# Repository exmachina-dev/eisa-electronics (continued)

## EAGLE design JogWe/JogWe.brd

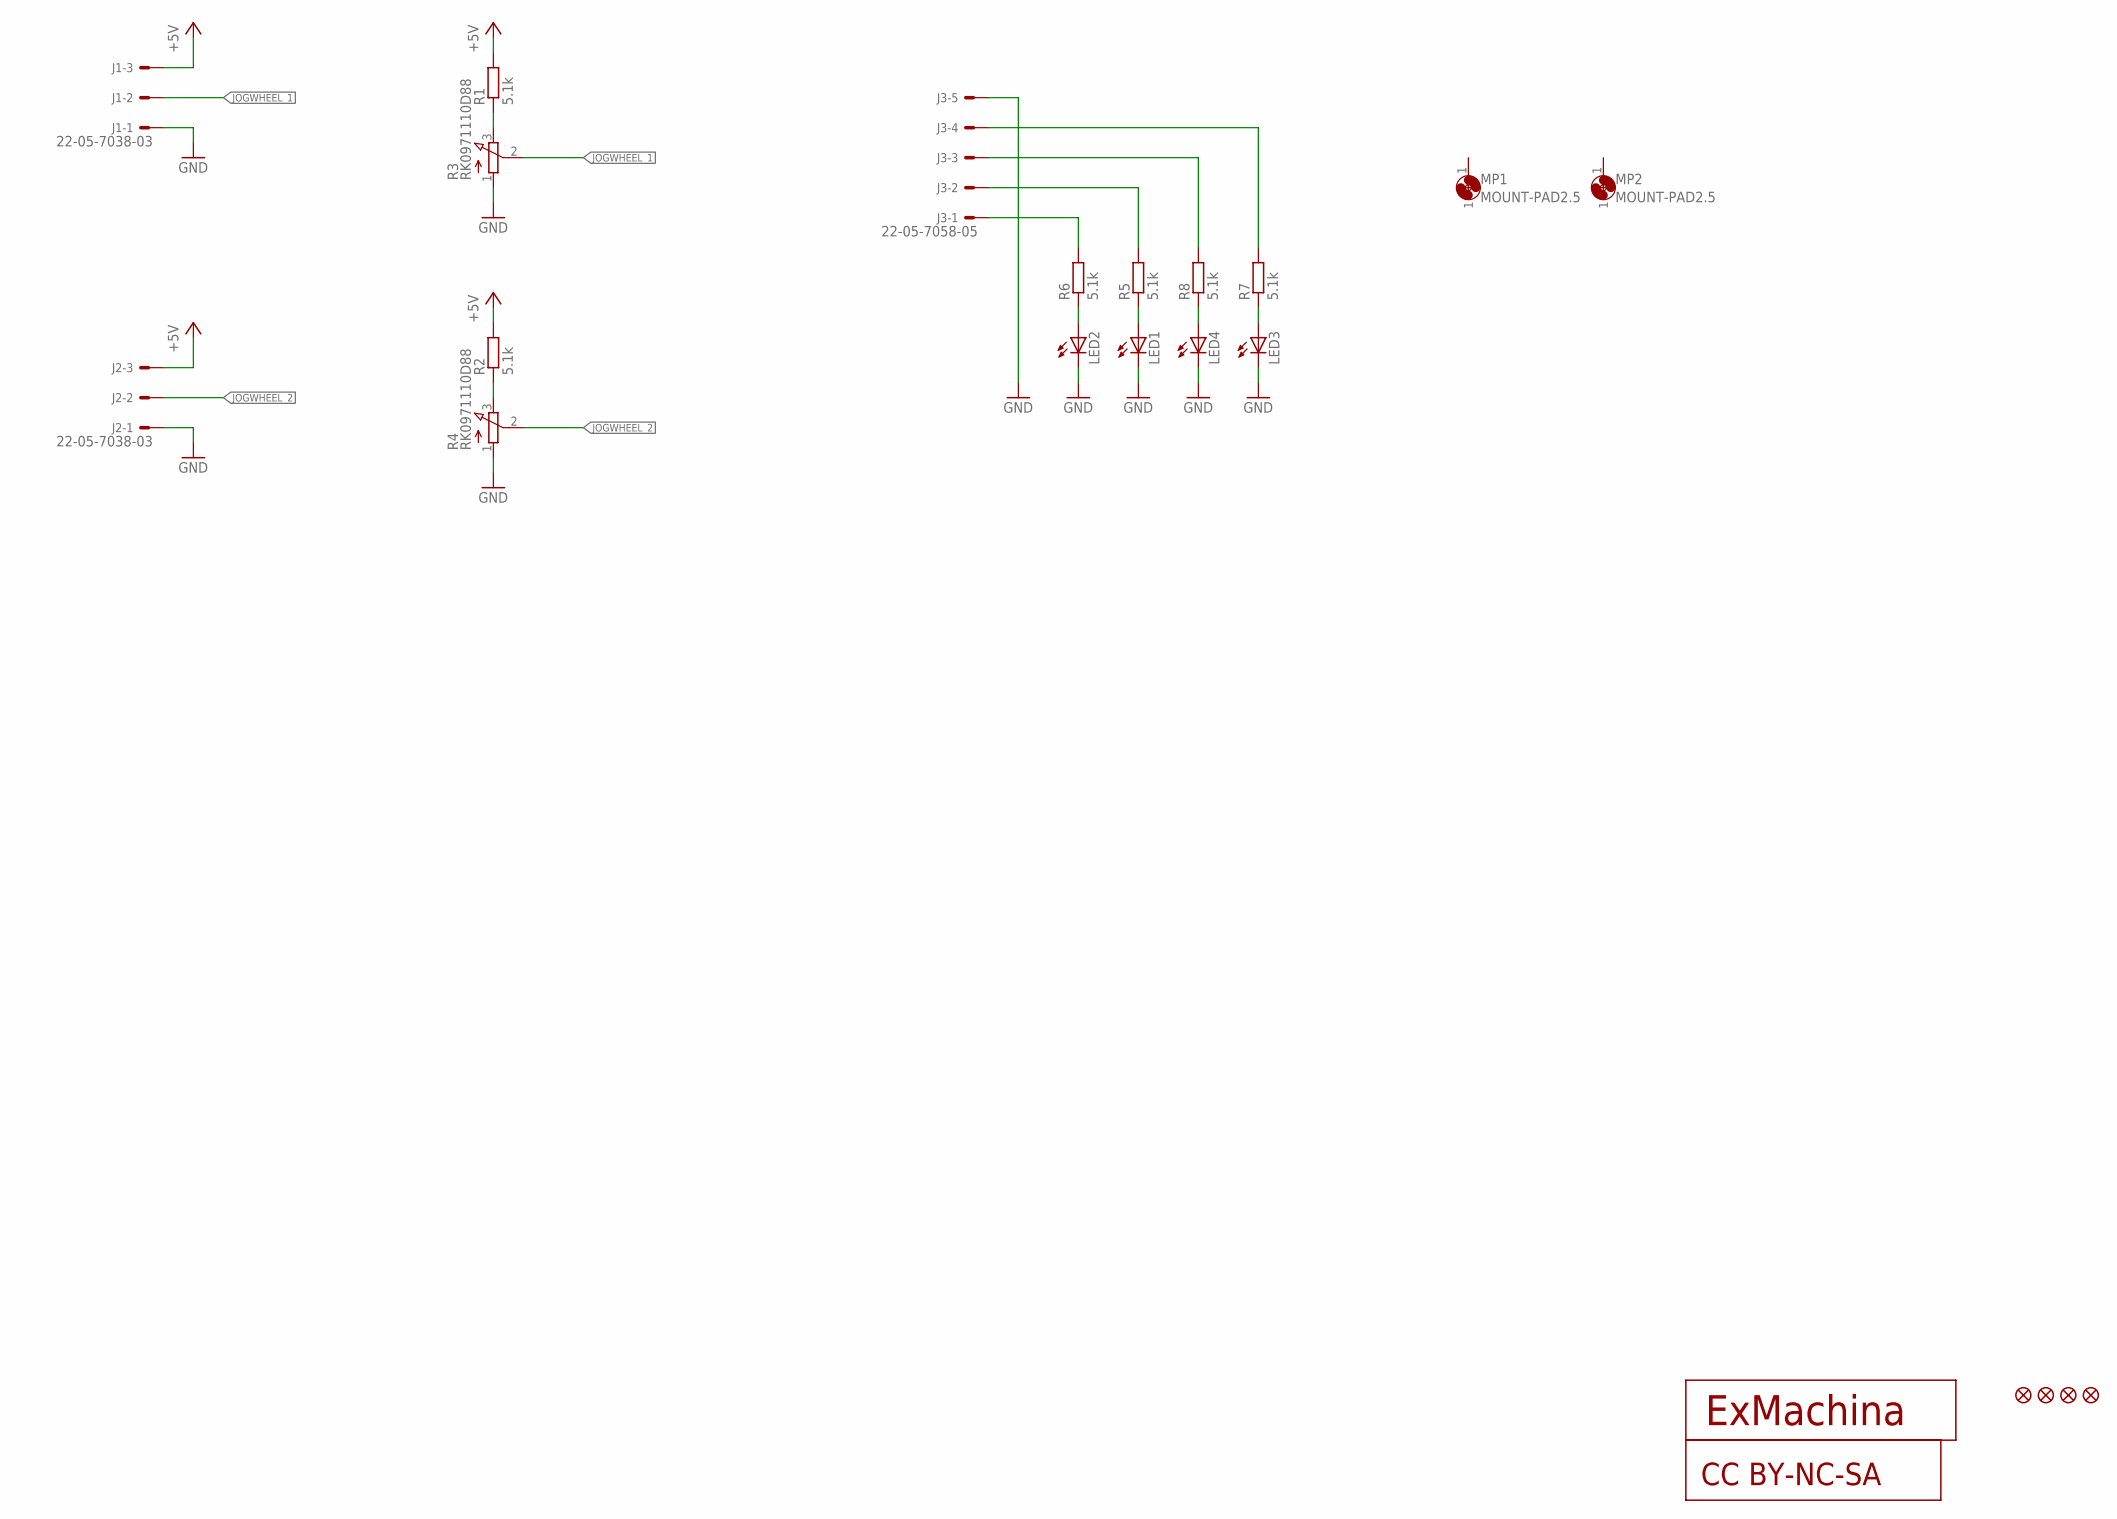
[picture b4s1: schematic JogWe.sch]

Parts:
J1, J2: 22-05-7038-03; 7395-03
J3: 22-05-7058-05; 7395-05
JP1, JP2, JP3, JP4: FIDUCIAL1X2; FIDUCIAL-1X2
LED1, LED2, LED3, LED4: LEDCHIP-LED0603; CHIP-LED0603
MP1, MP2: MOUNT-PAD2.5; P2.5
R1, R2, R5, R6, R7, R8: 5.1k; R0603
R3, R4: RK0971110D88; RK097
U$1: EXMACHINA-LOGO-NAME; EXM-LOGO-BASELINE
U$2: CC-BY-NC-SA

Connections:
+5V: J1.3, J2.3, R1.2, R2.2
GND: J1.1, J2.1, J3.5, LED1.C, LED2.C, LED3.C, LED4.C, R3.1 (A), R4.1 (A)
JOGWHEEL_1: J1.2, R3.2 (S)
JOGWHEEL_2: J2.2, R4.2 (S)
unnamed: R1.1, R3.3 (E)
unnamed: R2.1, R4.3 (E)
unnamed: LED1.A, R5.1
unnamed: LED2.A, R6.1
unnamed: LED3.A, R7.1
unnamed: LED4.A, R8.1
unnamed: J3.4, R7.2
unnamed: J3.1, R6.2
unnamed: J3.2, R5.2
unnamed: J3.3, R8.2

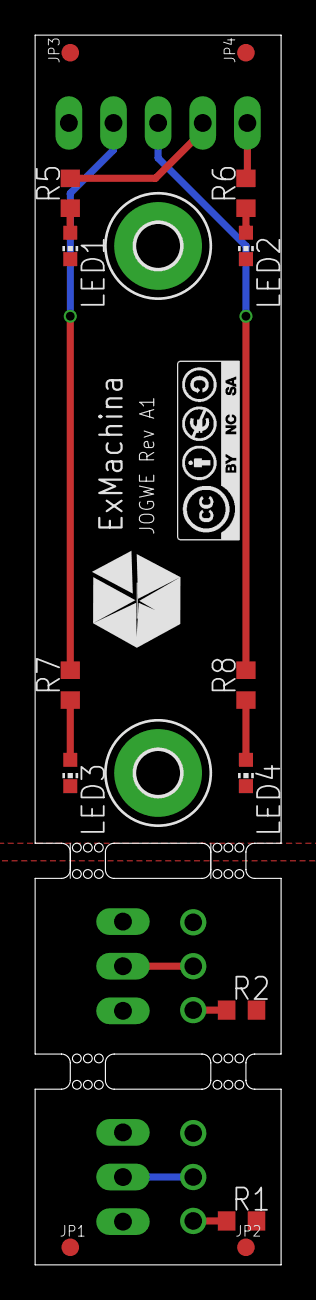
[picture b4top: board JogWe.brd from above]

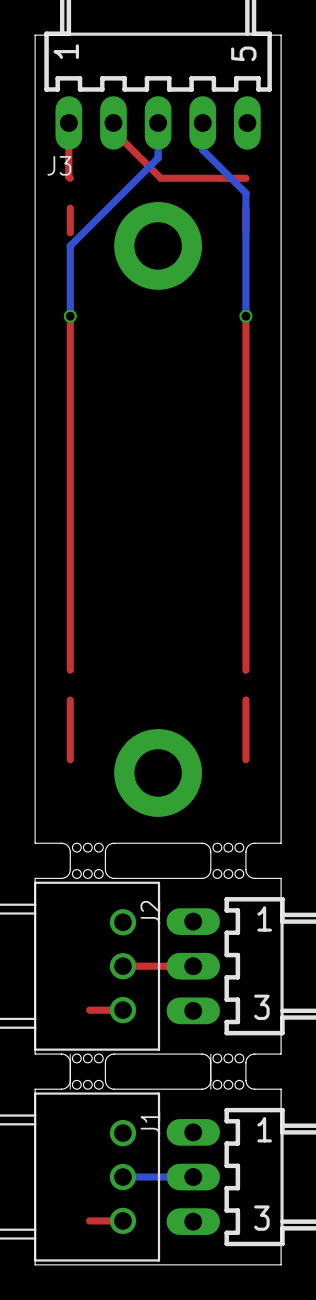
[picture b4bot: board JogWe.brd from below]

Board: 2 copper layers, 14.0 x 70.0 mm, 23 parts (5 on the bottom side), 14 nets.

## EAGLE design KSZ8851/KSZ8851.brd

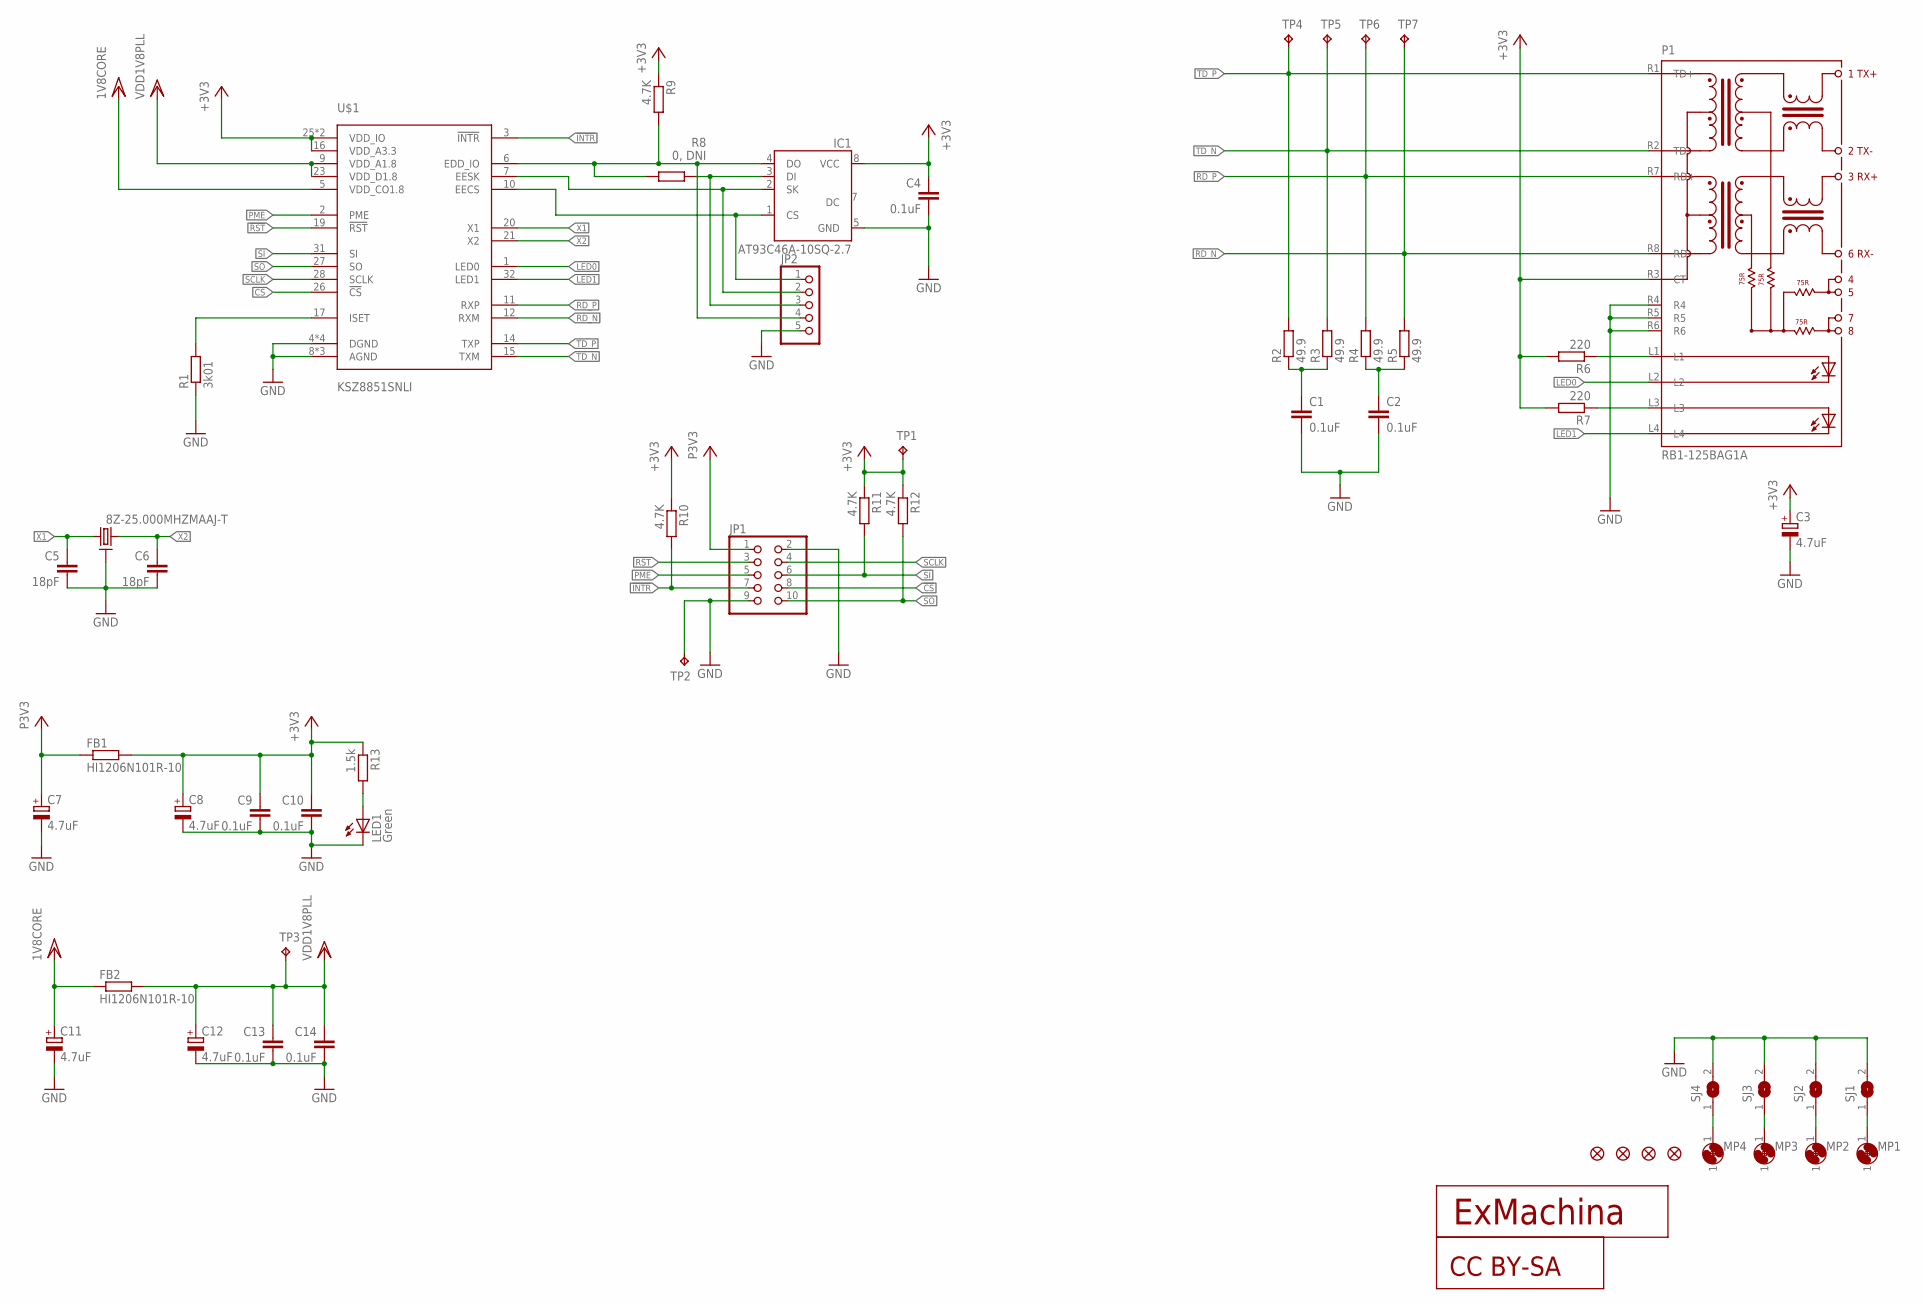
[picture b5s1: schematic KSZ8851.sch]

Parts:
-25.000MHZMAAJ-T1: 8Z-25.000MHZMAAJ-T; SMD2.5X2
C1, C2, C4, C9, C10, C13, C14: 0.1uF; C0603
C3, C7, C8, C11, C12: 4.7uF; CT3216
C5, C6: 18pF; C0603
FB1, FB2: HI1206N101R-10; 1206
IC1: AT93C46A-10SQ-2.7; SOIC8
JP1: PINHD-2X5; 2X05
JP2: PINHD-1X55X2MM; 1_05X2MM
JP3, JP4, JP5, JP6: FIDUCIAL1X2; FIDUCIAL-1X2
LED1: Green; SML0603
MP1, MP2, MP3, MP4: MOUNT-PAD2.5; P2.5
P1: RB1-125BAG1A; WIZNET_RB1-125BAG1A
R1: 3k01; R0603
R2, R3, R4, R5: 49.9; R0603
R6, R7: 220; R0603
R8: 0, DNI; R0603
R9, R10, R11, R12: 4.7K; R0603
R13: 1.5k; R0603
SJ1, SJ2, SJ3, SJ4: SJ
TP1, TP2, TP3: TPB2,54; B2,54
TP4, TP5, TP6, TP7: TPB1,27; B1,27
U$1: KSZ8851SNLI; QFN50P500X500X85-32L
U$2: EXMACHINA-LOGO-NAME; EXM-LOGO-BASELINE
U$3: CC-BY-SA

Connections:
1: MP1.1, MP2.1, MP3.1, MP4.1, SJ1.1, SJ2.1, SJ3.1, SJ4.1
!CS: JP1.8, U$1.26 (!CS)
!INTR: JP1.7, R10.2, U$1.3 (!INTR)
!RST: JP1.3, U$1.19 (!RST)
+3V3: C3.+, C4.1, C8.+, C9.1, C10.1, FB1.2, IC1.8 (VCC), P1.R3 (CT), R6.2, R7.2, R9.1, R10.1, R11.1, R12.1, R13.1, TP1.TP, U$1.16 (VDD_A3.3), U$1.25 (VDD_IO), U$1.30 (VDD_IO)
EECS: IC1.1 (CS), JP2.1, U$1.10 (EECS)
EEDIO: IC1.4 (DO), JP2.4, R8.2, R9.2, U$1.6 (EDD_IO)
EESK: IC1.2 (SK), JP2.2, U$1.7 (EESK)
GND: -25.000MHZMAAJ-T1.2, -25.000MHZMAAJ-T1.4 (2), C1.2, C2.2, C3.-, C4.2, C5.2, C6.2, C7.-, C8.-, C9.2, C10.2, C11.-, C12.-, C13.2, C14.2, IC1.5 (GND), JP1.2, JP1.9, JP2.5, LED1.C, P1.R4, P1.R5, P1.R6, R1.1, SJ1.2, SJ2.2, SJ3.2, SJ4.2, TP2.TP, U$1.4 (DGND), U$1.8 (AGND), U$1.13 (AGND), U$1.18 (AGND), U$1.22 (DGND), U$1.24 (DGND), U$1.29 (DGND)
LED0: P1.L2, U$1.1 (LED0)
LED1: P1.L4, U$1.32 (LED1)
unnamed: R1.2, U$1.17 (ISET)
unnamed: P1.L3, R7.1
unnamed: P1.L1, R6.1
unnamed: LED1.A, R13.2
unnamed: C1.1, R2.1, R3.1
unnamed: C2.1, R4.1, R5.1
unnamed: IC1.3 (DI), JP2.3, R8.1
PME: JP1.5, U$1.2 (PME)
RD_N: P1.R8 (RD-), R5.2, TP7.TP, U$1.12 (RXM)
RD_P: P1.R7 (RD+), R4.2, TP6.TP, U$1.11 (RXP)
SCLK: JP1.4, U$1.28 (SCLK)
SI: JP1.6, R11.2, U$1.31 (SI)
SO: JP1.10, R12.2, U$1.27 (SO)
TD_N: P1.R2 (TD-), R3.2, TP5.TP, U$1.15 (TXM)
TD_P: P1.R1 (TD+), R2.2, TP4.TP, U$1.14 (TXP)
VCC: C7.+, FB1.1, JP1.1
VCC/2: C11.+, FB2.1, U$1.5 (VDD_CO1.8)
VDD: C12.+, C13.1, C14.1, FB2.2, TP3.TP, U$1.9 (VDD_A1.8), U$1.23 (VDD_D1.8)
X1: -25.000MHZMAAJ-T1.1, C5.1, U$1.20 (X1)
X2: -25.000MHZMAAJ-T1.3, C6.1, U$1.21 (X2)

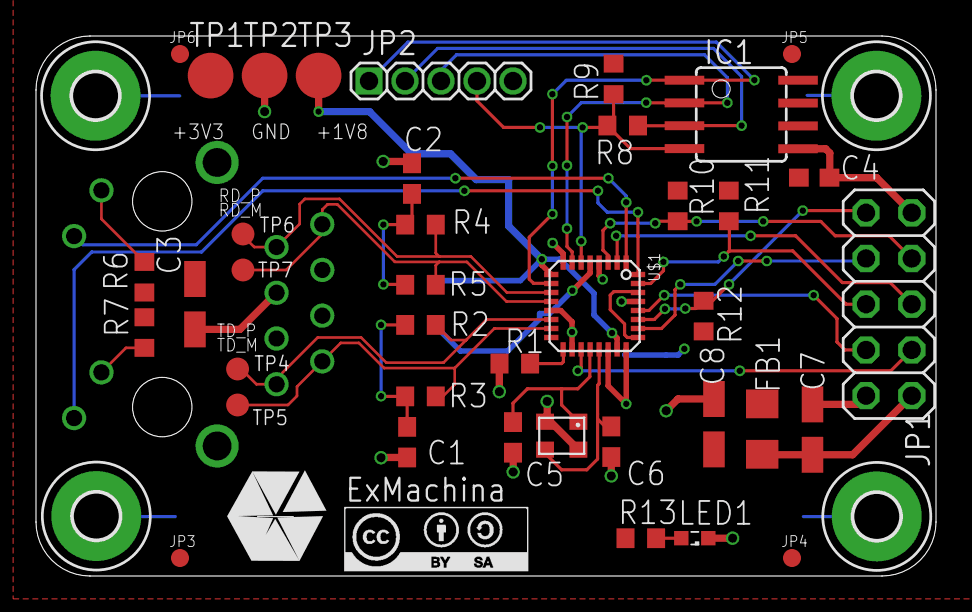
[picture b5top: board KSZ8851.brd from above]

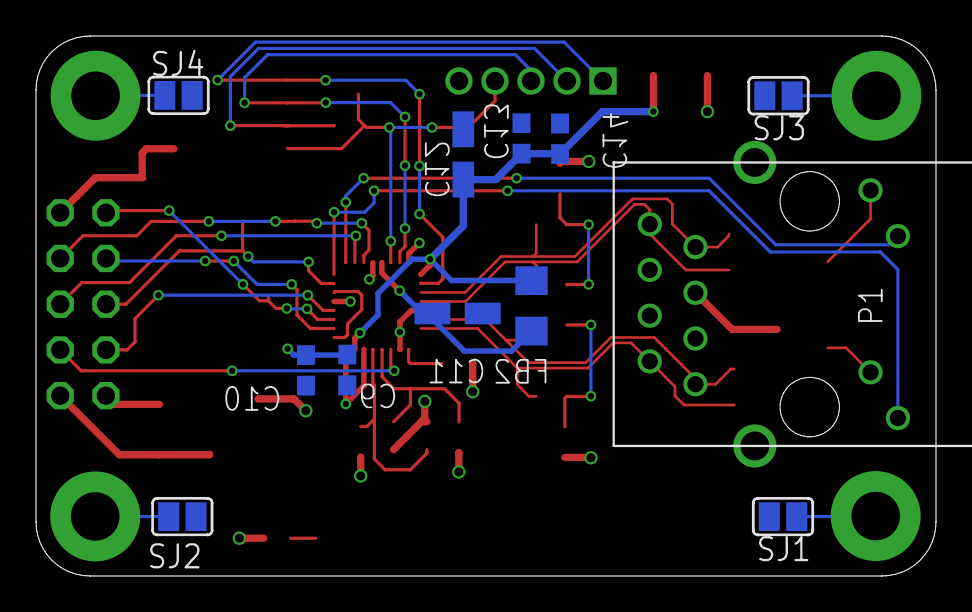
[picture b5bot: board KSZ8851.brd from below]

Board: 2 copper layers, 50.0 x 30.0 mm, 57 parts (12 on the bottom side), 31 nets.
